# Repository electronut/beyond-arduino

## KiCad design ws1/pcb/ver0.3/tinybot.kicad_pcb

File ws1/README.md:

## Introductory workshop.

- Attiny84
- avrdude/WinAVR
- USB ASP programmer
- Makefile
- LED blink
- PWM
- Ultrasonic sensor
- L293D
- 2WD Chassis

## Applications of tinyDriver

- 2WD robot
- Laser Display (rotating mirrors)
- Servos?

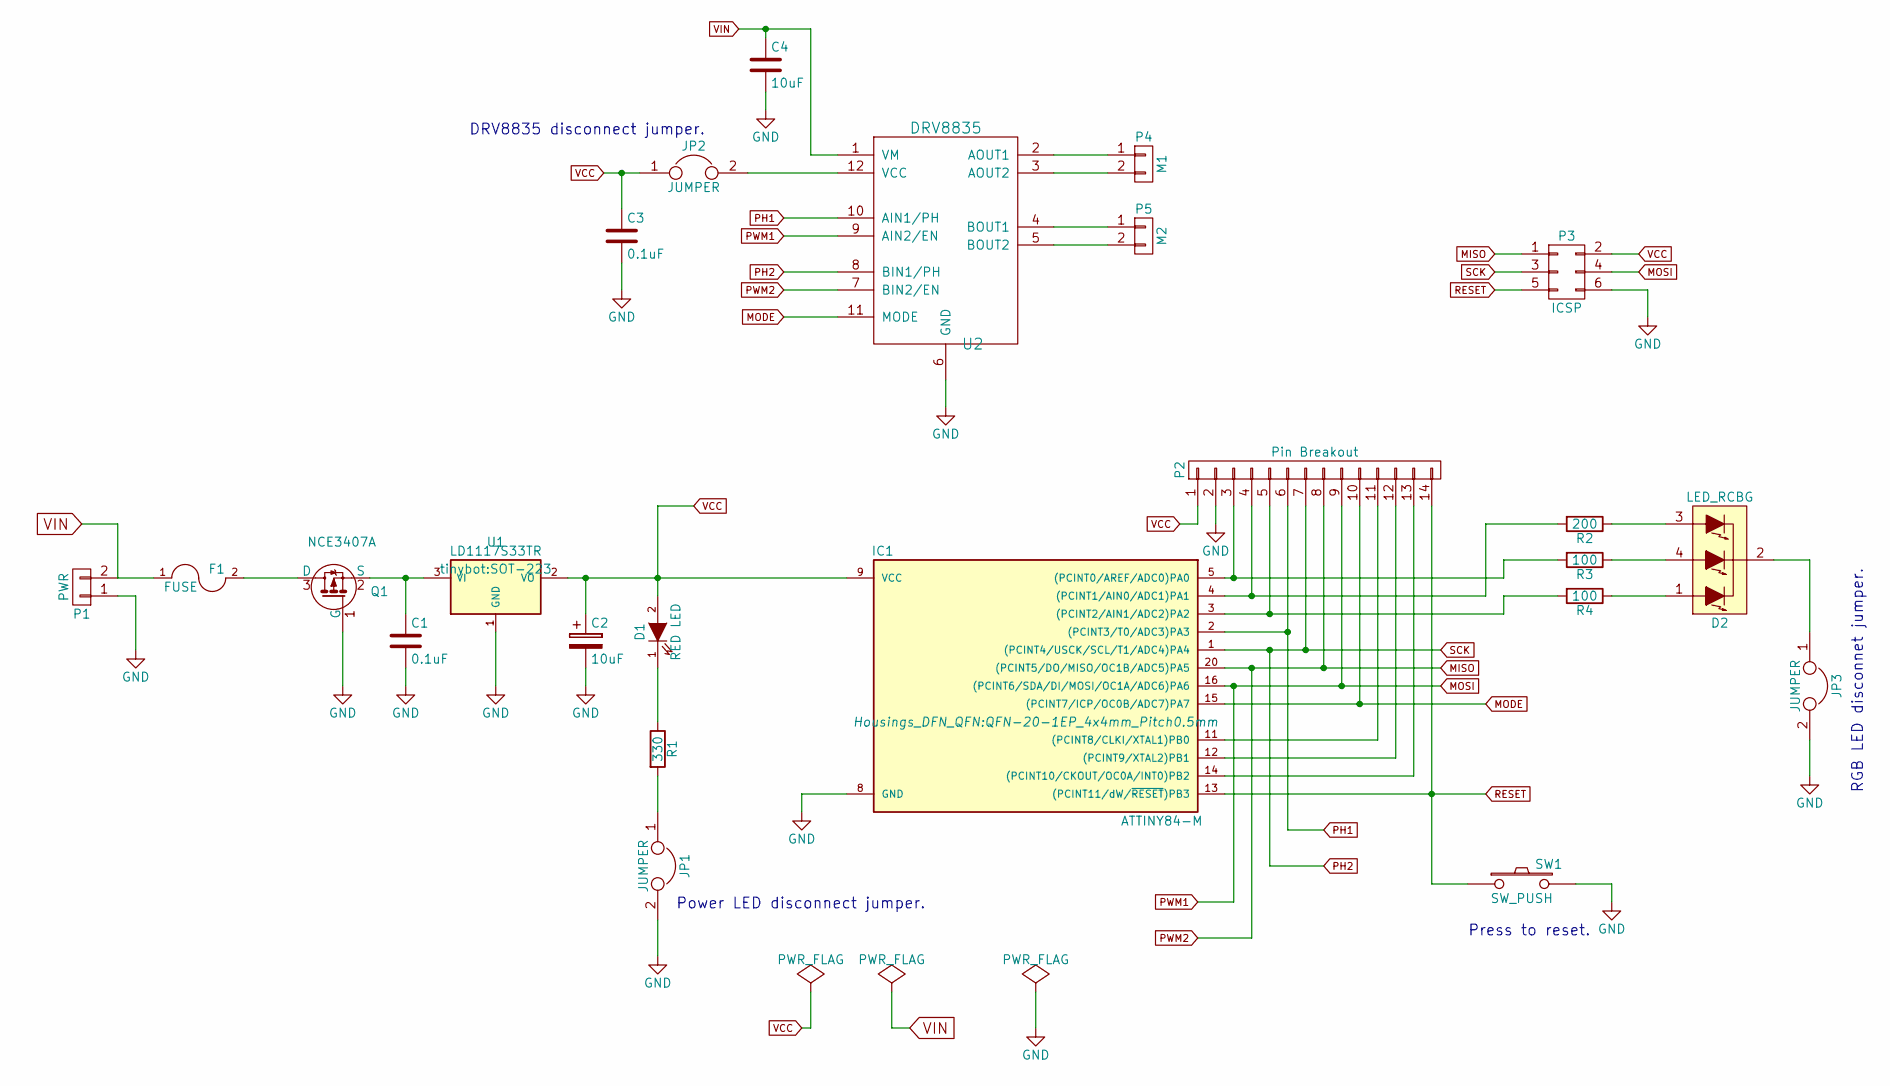
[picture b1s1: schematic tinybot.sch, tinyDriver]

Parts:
C1, C3: 0.1uF; C_0603
C2, C4: 10uF; C_0603
D1: RED LED; LED_1206
D2: LED_RCBG; LED-RGB-5MM_Common_Cathode
F1: FUSE; Fuse_SMD1206_Reflow
IC1: ATTINY84-M; QFN-20-1EP_4x4mm_Pitch0.5mm
JP1, JP2, JP3: JUMPER; C_0402
P1: PWR; TerminalBlock_Pheonix_MPT-2.54mm_2pol
P2: Pin Breakout; Pin_Header_Straight_1x14
P3: ICSP; Pin_Header_Straight_2x03
P4: M1; TerminalBlock_Pheonix_MPT-2.54mm_2pol
P5: M2; TerminalBlock_Pheonix_MPT-2.54mm_2pol
Q1: NCE3407A; SOT-23
R1: 330; R_0603
R2: 200; R_0603
R3, R4: 100; R_0603
SW1: SW_PUSH; SWITCH_SKQGAKE010
U1: LD1117S33TR; SOT-223
U2: DRV8835

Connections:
GND: C1.2, C2.2, C3.2, C4.2, IC1.8 (GND), JP1.2, JP3.2, P1.1, P2.2, P3.6, Q1.1 (G), SW1.2, U1.1 (GND), U2.6 (GND)
MISO: IC1.20 ((PCINT5/DO/MISO/OC1B/ADC5)PA5), P2.8, P3.1, U2.7 (BIN2/EN)
MODE: IC1.15 ((PCINT7/ICP/OC0B/ADC7)PA7), P2.10, U2.11 (MODE)
MOSI: IC1.16 ((PCINT6/SDA/DI/MOSI/OC1A/ADC6)PA6), P2.9, P3.4, U2.9 (AIN2/EN)
unnamed: C1.1, Q1.2 (S), U1.3 (VI)
unnamed: D1.1 (K), R1.1
unnamed: D2.1 (RED_ANODE), R4.1
unnamed: D2.2 (COMMON_CATHODE), JP3.1
unnamed: D2.3 (BLUE_ANODE), R2.1
unnamed: D2.4 (GREEN_ANODE), R3.1
unnamed: F1.2, Q1.3 (D)
unnamed: IC1.3 ((PCINT2/AIN1/ADC2)PA2), P2.5, R4.2
unnamed: IC1.4 ((PCINT1/AIN0/ADC1)PA1), P2.4, R2.2
unnamed: IC1.5 ((PCINT0/AREF/ADC0)PA0), P2.3, R3.2
unnamed: IC1.11 ((PCINT8/CLKI/XTAL1)PB0), P2.11
unnamed: IC1.12 ((PCINT9/XTAL2)PB1), P2.12
unnamed: IC1.14 ((PCINT10/CKOUT/OC0A/INT0)PB2), P2.13
unnamed: JP1.1, R1.2
unnamed: JP2.2, U2.12 (VCC)
unnamed: P4.1, U2.2 (AOUT1)
unnamed: P4.2, U2.3 (AOUT2)
unnamed: P5.1, U2.4 (BOUT1)
unnamed: P5.2, U2.5 (BOUT2)
PH1: IC1.2 ((PCINT3/T0/ADC3)PA3), P2.6, U2.10 (AIN1/PH)
PH2: IC1.1 ((PCINT4/USCK/SCL/T1/ADC4)PA4), P2.7, P3.3, U2.8 (BIN1/PH)
RESET: IC1.13 ((PCINT11/dW/~RESET~)PB3), P2.14, P3.5, SW1.1
VCC: C2.1, C3.1, D1.2 (A), IC1.9 (VCC), JP2.1, P2.1, P3.2, U1.2 (VO)
VIN: C4.1, F1.1, P1.2, U2.1 (VM)

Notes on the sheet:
Power LED disconnect jumper.
DRV8835 disconnect jumper.
RGB LED disconnet jumper.
Press to reset.

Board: 2 copper layers, 24 parts (0 on the bottom side), 28 nets, no tracks yet.

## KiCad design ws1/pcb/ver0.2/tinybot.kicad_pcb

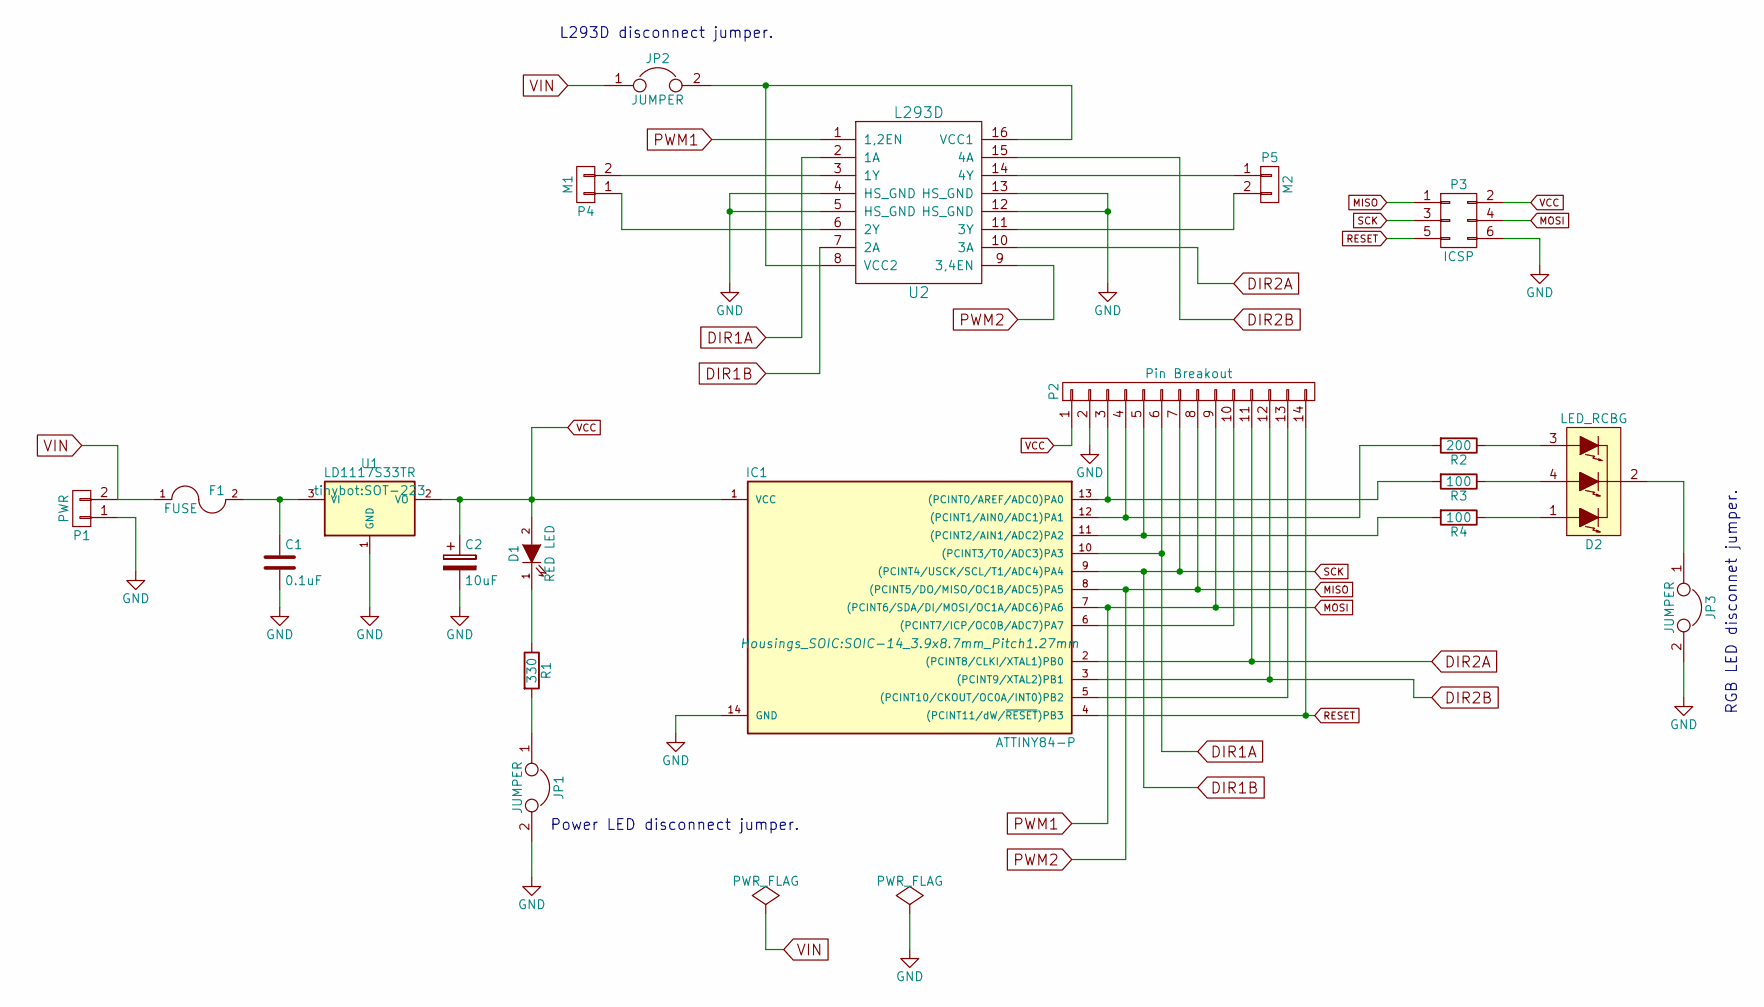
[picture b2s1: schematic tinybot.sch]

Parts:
C1: 0.1uF; C_0603
C2: 10uF; C_0603
D1: RED LED; LED_1206
D2: LED_RCBG; LED-RGB-5MM_Common_Cathode
F1: FUSE; Fuse_SMD1206_Reflow
IC1: ATTINY84-P; SOIC-14_3.9x8.7mm_Pitch1.27mm
JP1, JP2, JP3: JUMPER; C_0402
P1: PWR; TerminalBlock_Pheonix_MPT-2.54mm_2pol
P2: Pin Breakout; Pin_Header_Straight_1x14
P3: ICSP; Pin_Header_Straight_2x03
P4: M1; TerminalBlock_Pheonix_MPT-2.54mm_2pol
P5: M2; TerminalBlock_Pheonix_MPT-2.54mm_2pol
R1: 330; R_0603
R2: 200; R_0603
R3, R4: 100; R_0603
U1: LD1117S33TR; SOT-223
U2: L293D; SOIC-16_7.5x10.3mm_Pitch1.27mm

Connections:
DIR1A: IC1.10 ((PCINT3/T0/ADC3)PA3), P2.6, U2.2 (1A)
DIR1B: IC1.9 ((PCINT4/USCK/SCL/T1/ADC4)PA4), P2.7, P3.3, U2.7 (2A)
DIR2A: IC1.2 ((PCINT8/CLKI/XTAL1)PB0), P2.11, U2.10 (3A)
DIR2B: IC1.3 ((PCINT9/XTAL2)PB1), P2.12, U2.15 (4A)
GND: C1.2, C2.2, IC1.14 (GND), JP1.2, JP3.2, P1.1, P2.2, P3.6, U1.1 (GND), U2.4 (HS_GND), U2.5 (HS_GND), U2.12 (HS_GND), U2.13 (HS_GND)
MISO: IC1.8 ((PCINT5/DO/MISO/OC1B/ADC5)PA5), P2.8, P3.1, U2.9 (3,4EN)
MOSI: IC1.7 ((PCINT6/SDA/DI/MOSI/OC1A/ADC6)PA6), P2.9, P3.4, U2.1 (1,2EN)
unnamed: C1.1, F1.2, U1.3 (VI)
unnamed: D1.1 (K), R1.1
unnamed: D2.1 (RED_ANODE), R4.1
unnamed: D2.2 (COMMON_CATHODE), JP3.1
unnamed: D2.3 (BLUE_ANODE), R2.1
unnamed: D2.4 (GREEN_ANODE), R3.1
unnamed: IC1.5 ((PCINT10/CKOUT/OC0A/INT0)PB2), P2.13
unnamed: IC1.6 ((PCINT7/ICP/OC0B/ADC7)PA7), P2.10
unnamed: IC1.11 ((PCINT2/AIN1/ADC2)PA2), P2.5, R4.2
unnamed: IC1.12 ((PCINT1/AIN0/ADC1)PA1), P2.4, R2.2
unnamed: IC1.13 ((PCINT0/AREF/ADC0)PA0), P2.3, R3.2
unnamed: JP1.1, R1.2
unnamed: JP2.2, U2.8 (VCC2), U2.16 (VCC1)
unnamed: P4.1, U2.6 (2Y)
unnamed: P4.2, U2.3 (1Y)
unnamed: P5.1, U2.14 (4Y)
unnamed: P5.2, U2.11 (3Y)
RESET: IC1.4 ((PCINT11/dW/~RESET~)PB3), P2.14, P3.5
VCC: C2.1, D1.2 (A), IC1.1 (VCC), P2.1, P3.2, U1.2 (VO)
VIN: F1.1, JP2.1, P1.2

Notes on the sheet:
Power LED disconnect jumper.
L293D disconnect jumper.
RGB LED disconnet jumper.

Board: 2 copper layers, 20 parts (0 on the bottom side), 27 nets, no tracks yet.

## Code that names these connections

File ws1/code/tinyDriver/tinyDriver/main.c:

/*
tinyDriver - HCSR04 (Ultrasonic Sensor), DRV8835 (Motor Driver), RGB Led

HCSR04 uses timer0 with interrupt PCINT0. 
DRV8835 uses timer1 in Phase-Correct PWM mode.

Initially, tinyDriver moves forward. On obstacle detection within a range of 10 cms,
tinyDriver stops, reverses and takes a left turn.

*/

#define F_CPU 8000000

#include <avr/io.h>
#include <avr/interrupt.h>
#include <util/delay.h>

// GPIO pins HIGH to accelerate
void motorForward(int speed)
{
	PORTA &= 0x00;
	// non-inverting mode
	TCCR1A |= (1<<COM1A1)|(1<<COM1B1);
	PORTA |= 1<<PA7;
	PORTB |= 1<<PB2;
	OCR1A = OCR1B = speed;
	PORTA |= 1<<PA2;
}

//GPIO pins low to reverse 
void motorReverse(int speed)
{
	PORTA &= 0x00;
	// non-inverting mode
    TCCR1A |= (1<<COM1A1)|(1<<COM1B1);
	PORTA &= ~(1<<PA7);
	PORTB &= ~(1<<PB2);
	OCR1A = OCR1B = speed;	
	PORTA |= 1<<PA3;
}

// turn left
void motorLeft(int speed)
{
	PORTA &= 0x00;
	// non-inverting mode
	// left motor off, right motor on
	
	TCCR1A &= ~(1<<COM1A1);
	TCCR1A |= 1<<COM1B1;
	PORTB |= 1<<PB2;
	OCR1B = speed;
	PORTA |= ((1<<PA2)|(1<<PA3));
}

// turn right
void motorRight(int speed)
{
	PORTA &= 0x00;
	// non-inverting mode
	// left motor on, right motor off
	
	TCCR1A |= 1<<COM1A1;
	TCCR1A &= ~(1<<COM1B1);
	PORTA |= 1<<PA7;
	OCR1A = speed;
	PORTA |= ((1<<PA1)|(1<<PA2));
	
}

// turn off PWM o/p channels to stop
void motorStop()
{
	PORTA &= 0x00;
	TCCR1A &= ~((1<<COM1A1)|(1<<COM1B1));
	PORTA |= 1<<PA1;
}
int pinEcho = 0;
volatile char echoDone = 0;
uint32_t countTimer0 = 0;


//begin HCSR04
float getDistance()
{
	float distance = 0.0;
	
	cli();
	
	// interrupt enable
	GIMSK |= 1<<PCIE0;
	// enable pin
	PCMSK0 |= 1<<PCINT0;
	
	sei();
	
	// reset echo flag
	echoDone = 0;
	// reset counter
	countTimer0 = 0;
	
	// send 10us trigger pulse
	
	PORTB &= ~(1<<PB0);
	_delay_ms(20);
	PORTB |= (1<<PB0);
	_delay_ms(12);
	PORTB &= ~(1<<PB0);
	_delay_ms(20);
	
	// listen for echo
	while(!echoDone);
	
	// disable interrupt
	GIMSK &= ~(1<<PCIE0);
	// disable pin
	PCMSK0 &= ~(1<<PCINT0);

	// calculate duration
	float duration = countTimer0/8000000.0;
	
	// distance = duration * speed of sound * 0.5;
	// distance(in cms) = duration * 340.26 * 0.5 * 100
	// distance = 17013 * duration
	distance = 17013.0 * duration;
	
	return distance;	
}

// timer overflow handler
ISR(TIM0_OVF_vect)
{
	countTimer0 += 255;
}


//pin-change interrupt handler
ISR(PCINT0_vect)
{
	// read PCINT0
	if (PINA & (1<<PA0))
	{
		//start 16 bit timer
		// Divide by 1 - prescalar
		TCCR0B |= 1<<CS00;
		// set interrupt overflow flag
		TIMSK0 |= 1<<TOIE0;
	}
	else
	{
		// stop timer
		TCCR0B &= ~(1<<CS00);
		// calculate time elapsed
		countTimer0 += TCNT0;
		// reset counter - TCNT0
		TCNT0 = 0;
		// set flag
		echoDone = 1;
	}
}


int main(void)
{
	// pin set-up
	
	// PB0 - trigger
	// PB2 - GPIO for motor 2
	// PB1 - mode pin HIGH for phase enable in motor driver
	DDRB |= (1<<PB2)|(1<<PB1)|(1<<PB0);
	
	// PA1, PA2, PA3 = R,G,B leads of the LED
	// PA6, PA5 = OC1A, OC1B - PWM
	// PA7 = GPIO for motor 1, 
	DDRA |= (1<<PA7)|(1<<PA6)|(1<<PA5)|(1<<PA1)|(1<<PA2)|(1<<PA3);
	
	// Pull-up mode for PA0 - echo pin
	PORTB |= 1<<PB1;
	
	// TIMER0 PWM configurations
	// Phase Correct PWM, TOP = 0xFF
    TCCR1A |= (1<<WGM10);
	// CLK/8 pre-scalar for 2KHz motor frequency
	TCCR1B |= 1<<CS11;
	// register clear while in PWM mode
	TCCR1C = 0x00;
	
	float prevDist = 0.0;	
	while (1) 
    {	
		float dist = getDistance();
		if(dist>400)
		{
			dist = prevDist;
		}
	// prevDist = dist;
		if(dist>=10)
		{
		// no obstacle detected
		// move forward
			motorForward(150);	
		}
		else
		{
		// stop
			motorStop();
			_delay_ms(1000);
		
		// reverse
			motorReverse(150);
			_delay_ms(2000);
		
		// right turn
			motorRight(150);
			_delay_ms(1000);
			
		// left turn
		//	motorLeft(150);
		//	_delay_ms(1000);
				
		}
	}
	return 1;
}

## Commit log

2016-03-06 working on schematic
2016-03-07 added files on USBASP driver and ATtiny85 pdf
2016-03-07 logo added
2016-03-07 software directory removed
2016-03-07 documents removed as instructed
2016-03-07 added img
2016-03-08 switched to rgb led
2016-03-08 refining PCB
2016-03-10 switching to DRV8835
2016-03-10 switching to DRV8835 and qfn
2016-03-11 added mosfet
2016-03-11 ultrasonic and pwm test codes
2016-03-12 updated schematic and pcb added mounting holes
2016-03-12 updated docs
2016-03-15 motor driver + ultrasonic sensor interface to attiny84 successful
2016-03-17 tinyDriver completed code
2016-03-18 2wdbot added
2016-03-18 readme.md
2016-03-19 moving tinyDriver out
